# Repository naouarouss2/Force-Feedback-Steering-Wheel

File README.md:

# DIY FFB Steering Wheel
## What is it ? 🎮
A Force Feedback Wheelbase is a device used in car, truck, bus, or any other 3+ wheeled vehicle (as motorcycles require something different).

The difference between it and a standard game controller is, as the name suggests : **Force Feedback**

Force Feedback is what will create a physical connection between you and the game/simulator you're playing. It will allow you to feel every bump, road imperfection, steering stiffness, vibration... as if you're driving in real life.

## Features ✅
-  **Direct drive**, making it very silent, providing the most accurate and lossless feedback
-  **12-15Nm Force Feedback** (**5.7-7.1x** more powerful than the Logitech G29)
-  **12 Programmable buttons** (Depends on the wheel attached)
-  **Auto center**
-  **0.01125° sensitivity**, making it comparable to some high-end wheelbases on the market

## Why do I want to build it ? 🛠️
I have always wanted to have a simracing setup. Whenever I go to a mall or a gaming café and see a simracing setup, I run like a kid to try it.

I once tried a professional direct drive setup with a motion setup, and this really made me more excited about simracing.

The problem is that the only decent wheelbase available in Tunisia is the Logitech G29 family. They are pretty nice, but overpriced in Tunisia, and it really didn't really fill my heart and satisfy my requirements.

So I wanted to build my own wheelbase, tweaked to my likings and preferences, with endless upgrading and tuning options.

## 3D Design 🎨
I designed everything inside Solidworks, as I am pretty familiar with it, and I already have the CSWA certification.
I divided the design in 2 parts :
-  First, the wheelbase sub-assembly :

| **Full design** | **Aluminium machined parts** | **3D Printed parts** | **Commercial parts** |
|-----------------|------------------------------|----------------------|----------------------|
||||

-  Next, the steering wheel sub-assembly

| **Full design** | **Aluminium machined parts** | **3D Printed parts** | **Commercial parts** |
|-----------------|------------------------------|----------------------|----------------------|
|||||

And here are pictures of the finished product !

## Wheelbase PCB ⚡
To minimize wiring and make things simpler and cleaner inside, I made a PCB for the wheelbase

| **3D View** | **PCB Routing View** | **Schematics** | 
|-------------|----------------------|----------------|
||||

## Wiring Diagrams 🔌
### Wheelbase wiring diagram

### Steering wheel wiring diagram (made on KiCad, but no PCB)

## Wheelbase Firmware 💡
For the wheelbase, I will be using [OpenFFBoard](https://github.com/Ultrawipf/OpenFFBoard)

## Disclaimer ⚠️

**This project is still under development.**

**Some parts and dimensions in the design should be fixed when I get my hands on the actual componens.**

**Firmware is still untested.**

**This wheelbase can output very high amounts of torque, that may cause injuries.**

**Building is not recommended until everything is made safe ans stable, and the project is completed.**

**If you want to build this project before completion, I would recommend switching from aluminium paddle shifters to 3D Printed ones using the same STEP files, and starting with low force feedback power until the system feels familiar and reassuring, or better, until I finish the development and make sure that the project is safe to use.**

## License 🔓

This project is put opensource. 

Building as is, is allowed.

Remixing is also allowed, as long as the original project is linked and credited.

## Credits ❤️

Project made by **Oussama NAOUAR**

Total logged working time : **~68hrs**

Made as part of the **HackClub Blueprint** program, asking for a grant.

## BOM 💵

This table format below is slightly different from what I originally made in Google Sheets. To to understand it better, I would recommend checking out [BOM.pdf](BOM.pdf)

All prices and shippings costs below are shown in **USD**. For local Tunisian shops, prices and costs were **converted from TND to USD**, based on the exchange rates between **17-12-2025** and **16-12-2025**.

Prices shown below are **non-discounted** prices. These may vary, especially on Aliexpress and other non-local shops.

Shipping costs shown below are **indicative**, based on what Aliexpress and other non-local shops/manufacturers displayed. **These costs may change**.

Articles shown as (x2) are originally only sold as single items, not a 2pcs bundle, with a x2 quantity. And that is done to show the most accurate pricing and shipping fee.

|Type                    |Component name           |Product description                                                       |Shop / Manufacturer      |Local|URL                                                                                                                                     |Unit price|Shipping|Product Amount|Product Total (excluding shipping)|Product Total (with shipping)|
|------------------------|-------------------------|--------------------------------------------------------------------------|-------------------------|-----|----------------------------------------------------------------------------------------------------------------------------------------|----------|--------|--------------|----------------------------------|-----------------------------|
|Commercial parts        |20*20mm Aluminium Profile|Used to make the wheelbase frame                                          |Seli                     |Yes  |https://seli.tn/product/20x20-profile-aluminium-industriel-dk/                                                                          |15,6      |0       |1             |15,6                              |15,6                         |
|                        |40*20mm Aluminium Profile|Used to make the wheelbase frame                                          |Seli                     |Yes  |https://seli.tn/product/20x40-profile-aluminium-industriel-r6/                                                                          |22,5      |0       |1             |22,5                              |22,5                         |
|                        |SK16 Brackets            |Used to mount the motor in place                                          |Seli                     |Yes  |https://seli.tn/product/sk16-support-d-arbre-en-aluminium-diam-16/                                                                      |3,11      |0       |2             |6,22                              |6,22                         |
|                        |UFL004 Bearings          |Used to guide the shaft in rotation                                       |Aliexpress               |No   |https://ar.aliexpress.com/item/1005007098430647.html                                                                                    |17,9      |0       |1             |17,9                              |17,9                         |
|                        |ODESC 52V Driver         |Used to drive the motor and process FFB Logic                             |Aliexpress               |No   |https://ar.aliexpress.com/item/1005005763345874.html                                                                                    |78        |13,2    |1             |78                                |91,2                         |
|                        |STM32H743VIT6 Board      |Used to control the ODESC board along with the game inputs                |Aliexpress               |No   |https://ar.aliexpress.com/item/1005009563874211.html                                                                                    |11,55     |4,05    |1             |11,55                             |15,6                         |
|                        |2000PPR Rotary Encoder   |Used to determine the steering wheel's position                           |Aliexpress               |No   |https://ar.aliexpress.com/item/1005004387342695.html                                                                                    |15,35     |7,82    |1             |15,35                             |23,17                        |
|                        |30-tooth 30mm pulley     |Used to tie the encoder's shaft to the steering wheel shaft               |Aliexpress               |No   |https://ar.aliexpress.com/item/1005008678109995.html                                                                                    |4,67      |0       |1             |4,67                              |4,67                         |
|                        |Quick release mechanism  |Used to mount the steering wheel to the wheelbase                         |Aliexpress               |No   |https://ar.aliexpress.com/item/1005009121231549.html                                                                                    |62,86     |0       |1             |62,86                             |62,86                        |
|                        |GX12 Connector kit (M/F) |Used to connect input peripherals to the wheelbase                        |Tunisian Smart Innovation|Yes  |https://tuni-smart-innovation.com/products/connecteur-male-et-femelle-gx12-4-broches?_pos=1&_sid=6810da1da&_ss=r                        |1,49      |0       |5             |7,45                              |7,45                         |
|                        |120mm Fan                |Used to cool the wheelbase's electronics                                  |2BTrading                |Yes  |https://2btrading.tn/ventilateur-radiateur/2391-ventilateur-dc12v-034a-12x12x38cm.html                                                  |10,73     |        |1             |10,73                             |10,73                        |
|                        |XT60M connector          |Used to power the wheelbase                                               |Cothings                 |Yes  |https://cothings.net/products/connecteur-amass-xt60e-m-male                                                                             |1,73      |0       |1             |1,73                              |1,73                         |
|                        |Endstop switch           |Game inputs                                                               |Cothings                 |Yes  |https://cothings.net/products/copie-de-capteur-de-temperature-thermistance-ntc-100k-ntc-mf52at-1                                        |0,45      |0       |2             |0,9                               |0,9                          |
|                        |Pushbutton               |Game inputs                                                               |Cothings                 |Yes  |https://cothings.net/products/mini-bouton-poussoir-rond-a-reinitialisation-automatique-bleu-etanche-pbs-33b-12mm-2-broches              |0,86      |0       |8             |6,88                              |6,88                         |
|                        |Hall effect sensor       |Used to calibrate the wheel's initial position                            |Cothings                 |Yes  |https://cothings.net/products/ky-024-capteur-a-effet-hall-analogique-pour-vitesse-et-comptage                                           |1,55      |0       |1             |1,55                              |1,55                         |
|                        |36V 500W Power supply    |Used to power the wheelbase                                               |Aliexpress               |No   |https://ar.aliexpress.com/item/1005003923590693.html                                                                                    |50,53     |10,49   |1             |50,53                             |61,02                        |
|                        |GT2-6 400mm belt         |Used to connect the shaft pulley to the encoder pulley                    |2BTrading                |Yes  |Courroie GT2-6 400mm                                                                                                                    |3         |0       |1             |3                                 |3                            |
|                        |Seed XIAO RP2040         |Microcontroller for the steering wheel                                    |Aliexpress               |No   |https://ar.aliexpress.com/item/1005003682505451.html                                                                                    |4,78      |4,52    |1             |4,78                              |9,3                          |
|                        |Steering Wheel           |The actual steering wheel                                                 |Aliexpress               |No   |https://ar.aliexpress.com/item/1005009791304312.html                                                                                    |25,99     |42,53   |1             |25,99                             |68,52                        |
|                        |TJA1051                  |CAN transceiver                                                           |Aliexpress               |No   |https://ar.aliexpress.com/item/1005005569468051.html                                                                                    |4,1       |0       |1             |4,1                               |4,1                          |
|                        |12V Buck Converter       |Used to power the fan                                                     |Aliexpress               |No   |https://ar.aliexpress.com/item/1005008597548688.html                                                                                    |2,6       |7,28    |1             |2,6                               |12,48                        |
|                        |5V Buck Converter        |Used to power the MCU and other peripherals                               |Aliexpress               |No   |https://ar.aliexpress.com/item/1005008597548688.html                                                                                    |2,6       |        |1             |2,6                               |                             |
|                        |USB-C Female Connector   |Used to connect the wheelbase to the computer                             |Aliexpress               |No   |https://ar.aliexpress.com/item/1005009695057393.html                                                                                    |11,62     |0       |1             |11,62                             |11,62                        |
|                        |USB-C 90° cable          |Used to transfer the USB connection from the PCB to the external connector|Aliexpress               |No   |https://ar.aliexpress.com/item/1005002708307702.html                                                                                    |6,4       |4,79    |1             |6,4                               |11,19                        |
|                        |USB-C Breakout Board     |                                                                          |Aliexpress               |No   |https://ar.aliexpress.com/item/1005004807492800.html                                                                                    |4,19      |0       |1             |4,19                              |4,19                         |
|                        |JST-XH 4 Pin Connector   |Used to make cable connections easier                                     |Tunisian Smart Innovation|Yes  |https://tuni-smart-innovation.com/products/connecteur-jst-xh2-54-4-broches-male-femelle-avec-cable-de-20-cm?_pos=9&_sid=98b457343&_ss=r |0,7       |0       |5             |3.5                               |3.5                         |
|                        |JST-XH 3 Pin Connector   |Used to make cable connections easier                                     |Tunisian Smart Innovation|Yes  |https://tuni-smart-innovation.com/products/connecteur-jst-xh2-54-3-broches-male-femelle-avec-cable-de-20-cm?_pos=12&_sid=98b457343&_ss=r|0,62      |0       |1             |0,62                              |0,62                         |
|                        |JST-XH 2 Pin Connector   |Used to make cable connections easier                                     |Tunisian Smart Innovation|Yes  |https://tuni-smart-innovation.com/products/connecteur-jst-xh-2-broches-male-femelle-avec-cable-de-20-cm?_pos=7&_sid=98b457343&_ss=r     |0,49      |0       |1             |0,49                              |0,49                         |
|                        |M2X10 Screw              |Screw diameter = 2mm, length = 10mm                                       |Already have             |     |N/A                                                                                                                                     |0         |0       |4             |0                                 |0                            |
|                        |M3x10 Screw              |Screw diameter = 3mm, length = 10mm                                       |Already have             |     |N/A                                                                                                                                     |0         |0       |8             |0                                 |0                            |
|                        |M3x16 Screw              |Screw diameter = 3mm, length = 16mm                                       |Already have             |     |N/A                                                                                                                                     |0         |0       |10            |0                                 |0                            |
|                        |M4x8 Screw               |Screw diameter = 4mm, length = 8mm                                        |Already have             |     |N/A                                                                                                                                     |0         |0       |8             |0                                 |0                            |
|                        |M4x16 Screw              |Screw diameter = 4mm, length = 16mm                                       |Already have             |     |N/A                                                                                                                                     |0         |0       |4             |0                                 |0                            |
|                        |M5x16 Screw              |Screw diameter = 5mm, length = 16mm                                       |Already have             |     |N/A                                                                                                                                     |0         |0       |6             |0                                 |0                            |
|                        |M5x36 Screw              |Screw diameter = 5mm, length = 36mm                                       |Already have             |     |N/A                                                                                                                                     |0         |0       |4             |0                                 |0                            |
|                        |M5x50 Screw              |Screw diameter = 5mm, length = 50mm                                       |Already have             |     |N/A                                                                                                                                     |0         |0       |6             |0                                 |0                            |
|                        |M6x20 Screw              |Screw diameter = 6mm, length = 20mm                                       |Already have             |     |N/A                                                                                                                                     |0         |0       |4             |0                                 |0                            |
|                        |M10x16 Screw             |Screw diameter = 10mm, length = 16mm                                      |Already have             |     |N/A                                                                                                                                     |0         |0       |2             |0                                 |0                            |
|                        |M3 Nut                   |Nut diameter = 3mm                                                        |Already have             |     |N/A                                                                                                                                     |0         |0       |4             |0                                 |0                            |
|                        |M10 Nut                  |Nut diameter = 10mm                                                       |Already have             |     |N/A                                                                                                                                     |0         |0       |2             |0                                 |0                            |
|                        |M3 Aluminium Profile Nut |Nut for aluminium profiles, diameter = 3mm                                |Seli                     |Yes  |https://seli.tn/product/ecrou-marteau/                                                                                                  |0,1       |0       |4             |0,4                               |0,4                          |
|                        |M4 Aluminium Profile Nut |Nut for aluminium profiles, diameter = 4mm                                |Seli                     |Yes  |https://seli.tn/product/ecrou-marteau/                                                                                                  |0,1       |0       |8             |0,8                               |0,8                          |
|                        |M5 Aluminium Profile Nut |Nut for aluminium profiles, diameter = 5mm                                |Seli                     |Yes  |https://seli.tn/product/ecrou-marteau/                                                                                                  |0,1       |0       |4             |0,4                               |0,4                          |
|                        |M6 Aluminium Profile Nut |Nut for aluminium profiles, diameter = 6mm                                |Seli                     |Yes  |https://seli.tn/product/ecrou-marteau/                                                                                                  |0,1       |0       |4             |0,4                               |0,4                          |
|                        |Table clamps (x2)        |Used to mount the wheelbase on the table                                  |Aliexpress               |No   |https://ar.aliexpress.com/item/1005006458478718.html                                                                                    |47,8      |8,28    |1             |47,8                              |56,08                        |
|                        |Hoverboard motor         |Used to provide force feedback                                            |Facebook Marketplace     |Yes  |N/A                                                                                                                                     |19        |0       |1             |19                                |19                           |
|                        |TOTAL                    |                                                                          |                         |     |                                                                                                                                        |          |        |              |453,11                            |556,07                       |
|PCB                     |Wheelbase PCB            |Holds the various electronic components without the need for wiring       |JLC PCB                  |No   |N/A                                                                                                                                     |2         |21,91   |1             |2                                 |21,91                        |
|Aluminium machined parts|Front plate              |                                                                          |JLC CNC                  |No   |N/A                                                                                                                                     |8,72      |49,48   |1             |8,72                              |72,77                        |
|                        |Back plate               |                                                                          |JLC CNC                  |No   |N/A                                                                                                                                     |10,63     |        |1             |10,63                             |                             |
|                        |Paddle (x2)              |                                                                          |JLC CNC                  |No   |N/A                                                                                                                                     |3,94      |        |1             |3,94                              |                             |
|GRAND TOTAL             |                         |                                                                          |                         |     |                                                                                                                                        |          |        |              |478,4                             |650,75                       |

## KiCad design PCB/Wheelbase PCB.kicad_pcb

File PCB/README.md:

Here you will find all of the Wheelbase PCB files.

Extensions  :
-  Project : .kicad_pro
-  Schematic : .kicad_sch
-  PCB : .kicad_pcb
-  Footprint libraries created and used : .pretty
-  Symbol libraries created and used : .kicad_sym

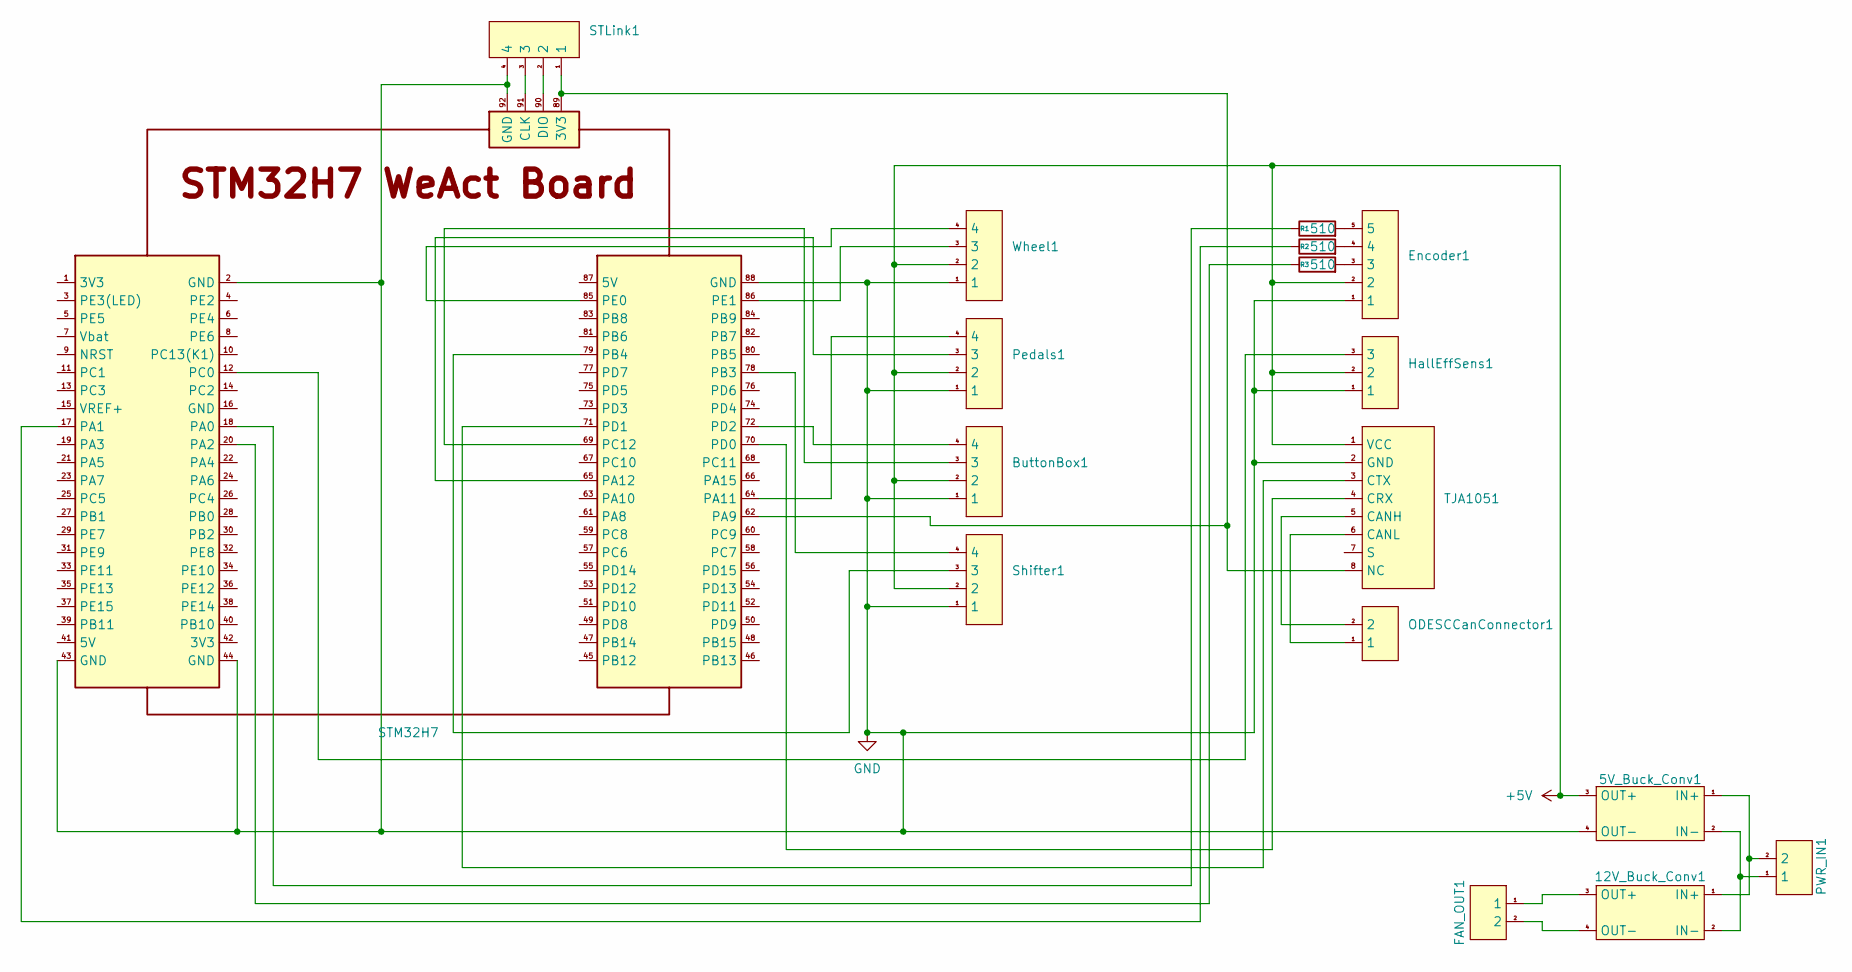
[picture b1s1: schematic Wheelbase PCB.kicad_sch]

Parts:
5V_Buck_Conv1, 12V_Buck_Conv1: Buck Converter
ButtonBox1: JST_XH_B4B-XH-A_1x04_P2.50mm_Vertical
Encoder1: JST_XH_B5B-XH-A_1x05_P2.50mm_Vertical
FAN_OUT1: JST_XH_B2B-XH-A_1x02_P2.50mm_Vertical
HallEffSens1: JST_XH_B3B-XH-A_1x03_P2.50mm_Vertical
ODESCCanConnector1: JST_XH_B2B-XH-A_1x02_P2.50mm_Vertical
PWR_IN1: JST_XH_B2B-XH-A_1x02_P2.50mm_Vertical
Pedals1: JST_XH_B4B-XH-A_1x04_P2.50mm_Vertical
R1, R2, R3: 510; R_Axial_DIN0207_L6.3mm_D2.5mm_P10.16mm_Horizontal
STLink1: JST_XH_B4B-XH-A_1x04_P2.50mm_Vertical
STM32H7: WeAct Board
Shifter1: JST_XH_B4B-XH-A_1x04_P2.50mm_Vertical
TJA1051: TJA1051 Board
Wheel1: JST_XH_B4B-XH-A_1x04_P2.50mm_Vertical

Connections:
+5V: 5V_Buck_Conv1.3 (OUT+), ButtonBox1.2, Encoder1.2, HallEffSens1.2, Pedals1.2, Shifter1.2, TJA1051.1 (VCC), Wheel1.2
GND: 5V_Buck_Conv1.4 (OUT-), ButtonBox1.1, Encoder1.1, HallEffSens1.1, Pedals1.1, STLink1.4, STM32H7.2 (GND), STM32H7.43 (GND), STM32H7.44 (GND), STM32H7.88 (GND), STM32H7.92 (GND), Shifter1.1, TJA1051.2 (GND), Wheel1.1
unnamed: 5V_Buck_Conv1.1 (IN+), 12V_Buck_Conv1.1 (IN+), PWR_IN1.2
unnamed: 5V_Buck_Conv1.2 (IN-), 12V_Buck_Conv1.2 (IN-), PWR_IN1.1
unnamed: 12V_Buck_Conv1.3 (OUT+), FAN_OUT1.1
unnamed: 12V_Buck_Conv1.4 (OUT-), FAN_OUT1.2
unnamed: Encoder1.3, R3.2
unnamed: Encoder1.4, R2.2
unnamed: Encoder1.5, R1.2
unnamed: STLink1.3, STM32H7.91 (CLK)
unnamed: STLink1.2, STM32H7.90 (DIO)
unnamed: R1.1, STM32H7.18 (PA0)
unnamed: R2.1, STM32H7.17 (PA1)
unnamed: R3.1, STM32H7.20 (PA2)
unnamed: STLink1.1, STM32H7.62 (PA9), STM32H7.89 (3V3), TJA1051.8 (NC)
unnamed: Pedals1.4, STM32H7.64 (PA11)
unnamed: Pedals1.3, STM32H7.65 (PA12)
unnamed: STM32H7.78 (PB3), Shifter1.4
unnamed: STM32H7.79 (PB4), Shifter1.3
unnamed: HallEffSens1.3, STM32H7.12 (PC0)
unnamed: ButtonBox1.3, STM32H7.69 (PC12)
unnamed: STM32H7.70 (PD0), TJA1051.4 (CRX)
unnamed: STM32H7.71 (PD1), TJA1051.3 (CTX)
unnamed: ButtonBox1.4, STM32H7.72 (PD2)
unnamed: STM32H7.85 (PE0), Wheel1.4
unnamed: STM32H7.86 (PE1), Wheel1.3
unnamed: ODESCCanConnector1.2, TJA1051.5 (CANH)
unnamed: ODESCCanConnector1.1, TJA1051.6 (CANL)

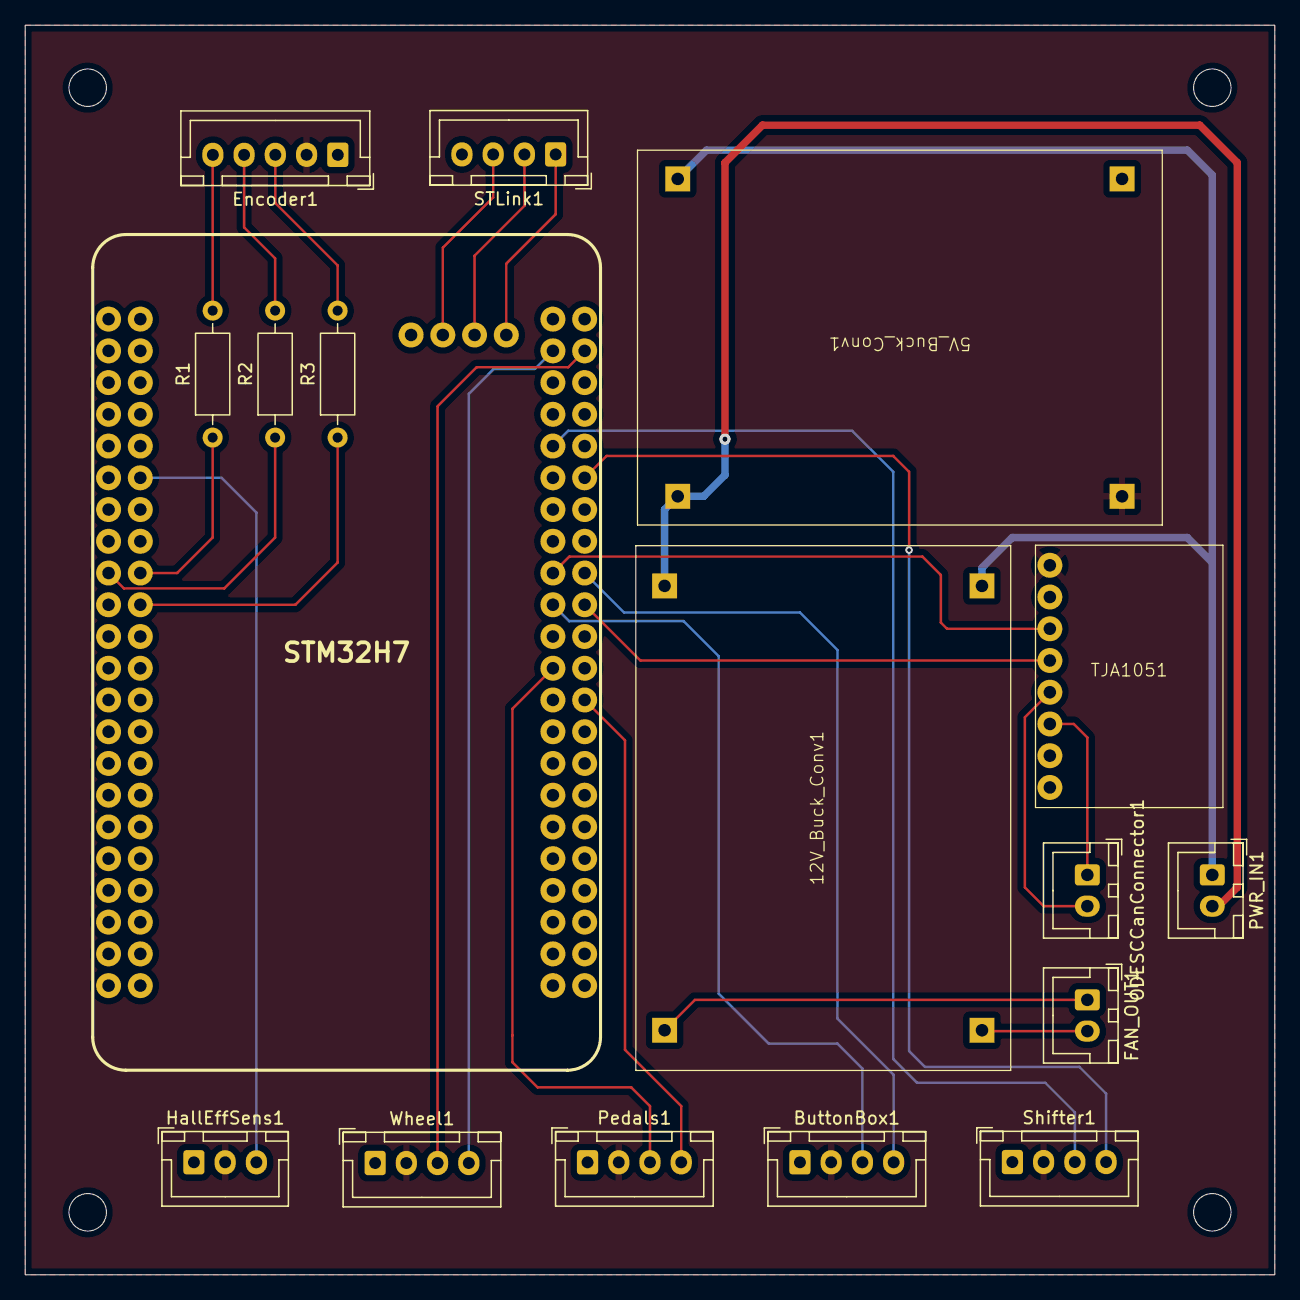
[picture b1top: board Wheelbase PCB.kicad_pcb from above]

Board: 4 copper layers, 100.0 x 100.0 mm, 17 parts (0 on the bottom side), 28 nets.

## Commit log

2026-01-17 Add README
2026-03-20 Add Wheelbase Firmware section to README
    Added section for Wheelbase Firmware using OpenFFBoard.
